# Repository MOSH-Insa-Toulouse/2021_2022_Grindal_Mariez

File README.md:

2021_2022_Grindal_Mariez_graphite_flex_sensor_project

# Objective of the project
The objective of the project is to design and build a PCB shield including a **low-tech graphite strain sensor** coupled to an analog electronic circuit that communicates data via a microcontroller to an Android application. The aim of this project is to get the resistance from a graphite sensor to measure a deformation, to analyze the results obtained and to describe the characteristics of the sensor in a datasheet.

# Main steps of the project
   [1. Graphite sensor conception](#1-graphite-sensor-conception)\
   [2. Electrical conception and simulation on *LTSpice*](#2-electronic-conception-and-test-on-ltspice)\
   [3. PCB conception and printing](#3-pcb-conception-on-kicad)\
   [4. Arduino code](#4-arduino-code)\
   [5. Application ANDROID](#5-apk-application)\
   [6. Test bed](#6-test-bed)\
   [7. Datasheet](#7-datasheet)\
   [8. Limits](#8-limits)

# 1. Graphite sensor conception
The first step is to make the graphite sensor with paper and a pencil. Pencil cores and lead mines used in mechanical pencils consist of a mixture clay and tiny scales of graphite that can slide on top of each other. The sensor outline is printed on a piece of thick printing paper, and the remaining work is simply to cut it out and fill in the dotted "U" shape with a pencil, as shown on the image below. 
<p align="center"> 

The upside is that is allows to adjust the amount of graphite by adding or erasing the pencil mark containing graphite. The downside is the difficulty of reproducing the same sensor with the same graphite layer thickness and density of graphite. An additional problem regarding graphite is presented below.

<div align="center">    

**Graphite grading scale problem**
    
<div align="left"> 
    
There exists different graphite grading scales, with the numerical scale and the HB scale the two most widely used. The HB scale goes from 9B to 9H, “H” to indicate a hard pencil and “B” to designate the blackness of the pencil’s mark, indicating a softer lead and a higher proportion of graphite.
    
The problem when trying to reproduce a sensor is the lack of a specific industry standard for the darkness of the mark to be left within the HB or any other hardness grade scale. That implies that a HB pencil from one brand will not necessarily leave the same mark as a HB pencil from another brand. Most manufacturers set their own internal standards for graphite hardness grades and some differences are regional. For example in Japan, consumers tend to prefer softer darker leads, so an HB lead produced in Japan is generally softer and darker than an HB from European producers.
    
Specifying the exact product and manufacturer in addition to the graphite grading can increase the reproductibilty of the sensor.
> This project uses graphite from BIC Criterium 550 pencils with the gradings 6B, 4B, B, H and 3H. Special STEIN HB lead mines from Pentel is also used. STEIN stands for "Strongest Technology by Enhanced SiO2 Integrated Network" and have a 10 % denser core than an average HB lead mine. This can result in a different resistance range than a normal HB pencil despite applying it the same way with the same thickness etc.

# 2. Electronic conception and test on *LTSpice*
The second step is to build the electrical circuit adapted to our case. Strain sensor is a passive sensor and needs a conditionner. The output signal od the sensor is very low and can be easily interfered by noise (from the circuit or external noise). The aim of this part is to chose the good components to have the good filters and amplifiers. We also have to take into account the chracteritic of the arduino uno card we are gonna use:
* Resolution 10 to 12 bits (1024 à 4096 points)
* Full scale (VRef) : 1.1 V to 5.0 V
* Max source impedance 1 kOhm to 10 kOhm
* Max sampling frequency 15 kHz to 2.4 MHz
 
Graphite sensor is supplied by 5 V and gives resistance values between 20 MΩ and 100 MΩ. Direct measurement of a 100 nA current does not seem feasible. We have to amplifiy the signal and to filter it.
The final electrical circuit chosen is the following:
<p align="center">

### Role of different components:
> R5 at the input protects the operational amplifier against electrostatic discharges (ESD), and together with C1 makes up a filter for voltage noises
> 
> C1 with R1 makes up a filter for the current noise
>
> R2 is replaceable, in order to allow an adaptaion of the full scale range (digital potentiometer)
>
> C4 with R3 makes up the active filter
>   
> C2 with R6 makes up the passive output filter
>   
> C3 filters out the power supply noise
>   
> The digital potentiometer MCP41050 can change the gain and adapt it to the resistance value from the graphite sensor. Resistance of the digital potentiometer can vary between 330 Ω and 50k Ω based on datasheet. 
 
### Sensor resistance calculation:
<p align="center">

### Low-pass filters
> For each electrical stage, we can simulate the cuttoff frequency by putting the capacity of each filter at zero:
> * Low-pass filter 1 (C4 = C2 = 0) : 16 kHz\
>      To select signals with frequency less than 10*1.5kHz (sample frequency of the arduino card) to respect Shannon criteria
> * Low-pass filter 2 (C1 = C2 = 0) : 2,1 kHz\
>      To filter noises from sector of the power supply at 50 Hz
> * Low-pass filter 3 (C1 = C4 = 0) : 1,6 kHz\
       To filter global external noises of voltage and current
 
### Main characteristics of the electrical circuit
> Global gain: from 3.13 to 127.9
>
> Global attenuation of a 50 Hz current noise: 100 dB or 10e5
>
> Offset of the LTC1050 is about 5 µV wich is acceptable because much lower than the voltage measured to ouputs of the resistance R1 of 10 mV (and the maximum offset voltage drift is about 0.05 μV/°C).

### Simulations on *LTSpice*
> Simulations on LT-Spice allowed us to:
> * To check the operation in nominal conditions
> * To check the operation in nominal conditions
> * To accept the impact of the LTC1050C amplifier offset
> * To accept the impact of the amplifier input current
> * To find the cuttoff frequency of each low-pass filter stage
> * To find the global attenuation of a 50 Hz current noise
> * To find the global attenuation of a current noise occurring at the aliasing limit frequency
>
> To check all these points, we did differents simulations:
> * In transient conditions, with a pulse signal from the sensor
> * In AC conditions, to see attenuation, gain and cuttoff frequencies
> * In transient conditions, with AC voltage generator to simuate 50 Hz noise.
> * In transient and AC conditions with resistance of the digital potentiometer varying from 1 kΩ to 15 kΩ (step of 1 kΩ) to see the influence of this component on ccircuit response.
<div align="center"> 

**Transient simulation with R2 varying between 1 kΩ to 15 kΩ**

   **Transient simulation with with R2 varying between 1 kΩ to 15 kΩ and noise at 50 Hz (oscillations)**
   <div align="left">   

> The digital potentiometer has a strong influence on electrical circuit. The gain is modified, but not into a linear way with potentiometer variation. The more the resistance is high, the less is the gain, and the worse is the output signal (see [Limits](#8-limits) section)

The folder 
   [Electrical simulations on LT-Spice](https://github.com/MOSH-Insa-Toulouse/2021_2022_Grindal_Mariez/tree/main/Electrical%20simulations%20on%20LT-Spice) 
   contains the LT-Spice files used into different simulations. 

# 3. PCB conception on _KiCad_
Once the electrical circuit is done, we have to make the PCB conception to get the final circuit. First, we did the schematic in *KiCad*. Then, we build the PCB plane by adding the references and dimensions of each components. The final step is to print the PCB card with different processes.
Circuit conception was made on *KiCad*. 
### Circuit schematic on *KiCad*
> The electrical circuit was made in KiCad. All pins and connections are established. For each components, we have to associate the print. For LTC1050, rotary encoder, digital potentiometer and OLED screen, we have to create our own print in our own library. The schematic is made from a model with Arduino Uno shield to have directtly the right pins and the good dimensions of the card.
>  
<p align="center">

### PCB conception on _KiCad_
> After doing the schematic, we draw the PCB with the previous dimensions :
> * Track length = 0.9 mm
> * Isolation width = 0.7 mm
> * Pad dimensions for OLED, Bluetooth module and rotary encoder = 2 mm * 2.5 mm
> * Drill size for OLED, bluetooth module, rotary encoder, AOP and digital potentiometer = 1 mm
> * Pad size for AOP and digital potentiometer = 1.8 mm * 2.5 mm
> * Drill size for resistances and capacities = 2 mm
> * Pad size for resistances and capacities = 0.8 mm
> For each component, we have to find the print associated or to make it into a new libary (for rotary encoder, OLED screen, LTC1050 and digital potentiomter). After placing the components in the optimal way, we trace the wires and make the ground plane.
> 
<p align="center">

### PCB 3D visualisation  
> 

> A 3D visualisation is possible and allowed us to well arrange components placement without spatial conflict. 

All *KiCad* files are in the folder [Projet2022_grindal_mariez_pcb](https://github.com/MOSH-Insa-Toulouse/2021_2022_Grindal_Mariez/tree/main/Projet2022_grindal_mariez_pcb)
   section.

### PCB printing processes
> Mask printed on transparent film (PCB plan from KICAD) 
>
> The mask is placed on a plate of copper convered with photo-sensitive film. The mask and the plate are insolated with UV. The black part of the mask protects the photo-sensitive resin from UV, and the clear zone of the mask reveals copper beacause photo-sensitive resin reacts with UV.
>
> PCB plate is washed with a developper solution (oxydied water) that reveals the PCB circuit
>
> PCB plate is placed in oxyde bath to remove the unwanted copper not protected by photo-sensitive zone left.
>
> PCB is washed and left to dry.

<div align="center"> 

**Final PCB circuit with all components and modules. The two wires (at right, in purple) are  \
   connected to the two pads of the graphite sensor with clamps.**
<div align="left"> 
    
# 4. Arduino code
### Improvement potential for Arduino code
> Make the code run faster and more smoothly by optimizing menu management code. This can be done by decreasing the lines of code for the OLED display and assure the switch button on the rotary encoder, which is not connected to an interrupt pin, is detected regardless of the speed of the executing loop.  The number of variables in use for the menu, submenu and blocking the rotary encoder when needed should be reduced. Suboptimal solutions to ensure the screen is refreshed correctly can be improved upon.
>
> Decrease the time interval between two measurements, currently at 700 ms, to see how fast it can measure and decrease response time.
    
### General structure of Arduino code
>The Arduino code (.ino) is written in C++ with an addition of special methods and functions.
The main text editing program used for this project is the Arduino Integrated Development Environment (IDE). It has a clean and simple interface with the option of showing a serial monitor and a serial plotter. The serial monitor is useful for checking the outcoming bytes from the board to the digital potentiometer MCP41050 and communication with the APK application via the Bluetooth module HC-05.
    
### Libraries used 
> SoftwareSerial.h for defining serial ports on specific pins, here used with the Bluetooth module and digital potentiometer.
>
> Adafruit_GFX.h and Adafruit_SSD1306.h for the I2C OLED display SBC-OLED01.
>
> Wire.h contain the definitions for I2C pins used to communicate with the OLED display.
>
> SPI.h is used to communicate with SPI devices, with Arduino as the master device. The Serial Peripheral Interface (SPI) is a synchronous serial data protocol and is used with the digital potentiometer.

### The Arduino code is divided into four parts:
>The first lines contain inclusions (#include) of libraries, definitions (#define), which is a C++ component that allows to give a name to a constant value before the program is compiled, and declarations of global variables.
>    
>The setup() function, which initializes and sets the initial values, is executed only one time after powering on the Arduino board. 
In this case, the mode of pins on the board are initialized with pinMode(), and digitalWrite() is used to turn on the pullup resistors for the rotary encoder KY-040. Data transfer through serial ports, SPI, SoftwareSerial and Serial, is enabled.
>    
>The loop() function is the main part and runs continuously after the setup until the reset button is pressed or the power supply is cut.
    It is far from optimized and contain a lot of if-statements. First it checks to detect a change in the switch button, then checks if the APK application has asked for measurement data or an updated Rcal value to update the gain. Then it does a measurement if the interval requirement is met. The last part of the loop is a mix of rotary encoder and OLED display to make the menu and submenu options work. 
>  
>The last part is constituted of definitions of the functions used in the loop function. Six functions are defined. 
>   * The first function reads the analog pin connected to the sensor called readSensor() and returns the voltage in the range 0–5 V. 
>   * Two functions manages the digital potentiometer, setPot() and potSwiper(). setPot() changes dig. pot. position and updates Rcal and gain. potSwiper() uses setPot() and takes a float as input, with the goal to land on approximately the right voltage by running through the positions to find an adequate resistance value. 
>   * The OLEDstartup() function is simply the startup screen sequence, lasting around two seconds.
>   * The last functions doEncoderA() and doEncoderB() is attached to interrupts on both pins for the rotary encoder and includes debouncing, ensuring a rapid and accurate response to manual rotation of the encoder. The variable maxRot ensures a circular list regardless of scrolling through the menu or manually adjusting the gain.

Arduino code is available in the [Arduino code](https://github.com/MOSH-Insa-Toulouse/2021_2022_Grindal_Mariez/tree/main/Arduino%20code)
   section.
  
# 5. APK application
The APK application, working on Android smartphones, is made with the free web application integrated development environment MIT App Inventor.The app communicates over Bluetooth with the HC-05 module mounted on the Arduino shield, and allows to measure and trace resistance and voltage over time.
Main features:
* Display measured voltage and resistance numerically and traced as a function of time
* Update gain if modified on the shield
* Save measured data points in a text file found in the paths "/savedRfile.txt" and "/savedVfile.txt"
    
<p align="center"> 

The application folders .apk and .api are  available in the [Application](https://github.com/MOSH-Insa-Toulouse/2021_2022_Grindal_Mariez/tree/main/Application)
   folder.
 
# 6. Test bed
The six sensors were tested under compressive and tensile deflection on cylindrical objects with a constant diameter. The test bed consisted of seven cylindral objects with each a diameter ranging from 7 cm to 1,15 cm. The contact surface was covered in paper to minimize interactions between the object and the graphite layer on the sensor under compressive deflection.

### Test procedure
> The sensor was connected to the shield with two alligator clips. Voltage measurements indicated if the start voltage was near the extreme values of the range 0-5 V, indicating signal saturation in case of very high voltage and no current flowing in case of 0 V. Saturation of the signal was handled by choosing the "set gain" option in the menu to automatically adjust the gain to start at around 1 V. No signal was fixed by applying more graphite on the dotted area of the sensor.
>
> The R0 at zero derformation was measured when the sensor was pressed flat.
>
> Each sensor was first tested under tensile deflection, that is the graphite facing away from the curvature, with the assumption that the compressive deflection is more damaging to the sensor. The tensile deflection increases the distance between the graphite layers and decreases the measured voltage. The measurements were done in the order of decreasing diameter, starting with the smallest deformation to bend the paper sensor as little as possible to avoid detoriation.
>
> Graphite was reapplied on top of the old layer and a new R0 was measured when pressed flat.
> The same procedure was repeated for the compressive deflection with the sensor laying on a flat surface graphite layer up and bent upwards around the object while pressing the object gently downwards close to the edge of the table where the alligator clips were aligned. To avoid smearing of the graphite layer, especially for the 4B and 6B pencils, minimal friction was ensured between the sensor and the paper covered object. It is possible that smearing would have a minimal impact because the layer applied was thick. The measurements were done in the order of decreasing diameter, starting with the smallest deformation. 
>
> For compressive deflection, sudden drops in voltages occured for some of the sensors when repedately bending around the smallest objects and inducing large deformations. In those cases, graphite was reapplied on top of the old layer, a new R0 was measured when pressed flat and a new measurement series was conducted starting with the largest object.
    
# 7. Datasheet
Datesheet is providing the main characteristics and technical specifications of the strain sensor. It is in the folder [Datasheet](https://github.com/MOSH-Insa-Toulouse/2021_2022_Grindal_Mariez/tree/main/Datasheet)
   of the repository. 

# 8. Limits
   Is important to notice the limits of the sensor and the innacuracy of the test measures. Here are main points to be studied or solved:
   * The digital potentiometer MCP41050 is perfectly adapted to the graphite sensor. It would be better to have a sensor with a resistance variation between 10 Ω to 15 Ω, as the MCP41010 from *Microchip* for example.
   * The mapping from 8 bits to 10 bits in arduino code may lead to a resolution loss, so we lose in quality for the signal. 
   * We need a switch button to interrupt in case of problems
   * Regarding test bed, we are never sure of the amount of deposited graphite and it is not uniform. Also, the graphite quantity variation is not linear with pencils changing. Finally, paper is damaged after several compression/tension, so the measures are never similar

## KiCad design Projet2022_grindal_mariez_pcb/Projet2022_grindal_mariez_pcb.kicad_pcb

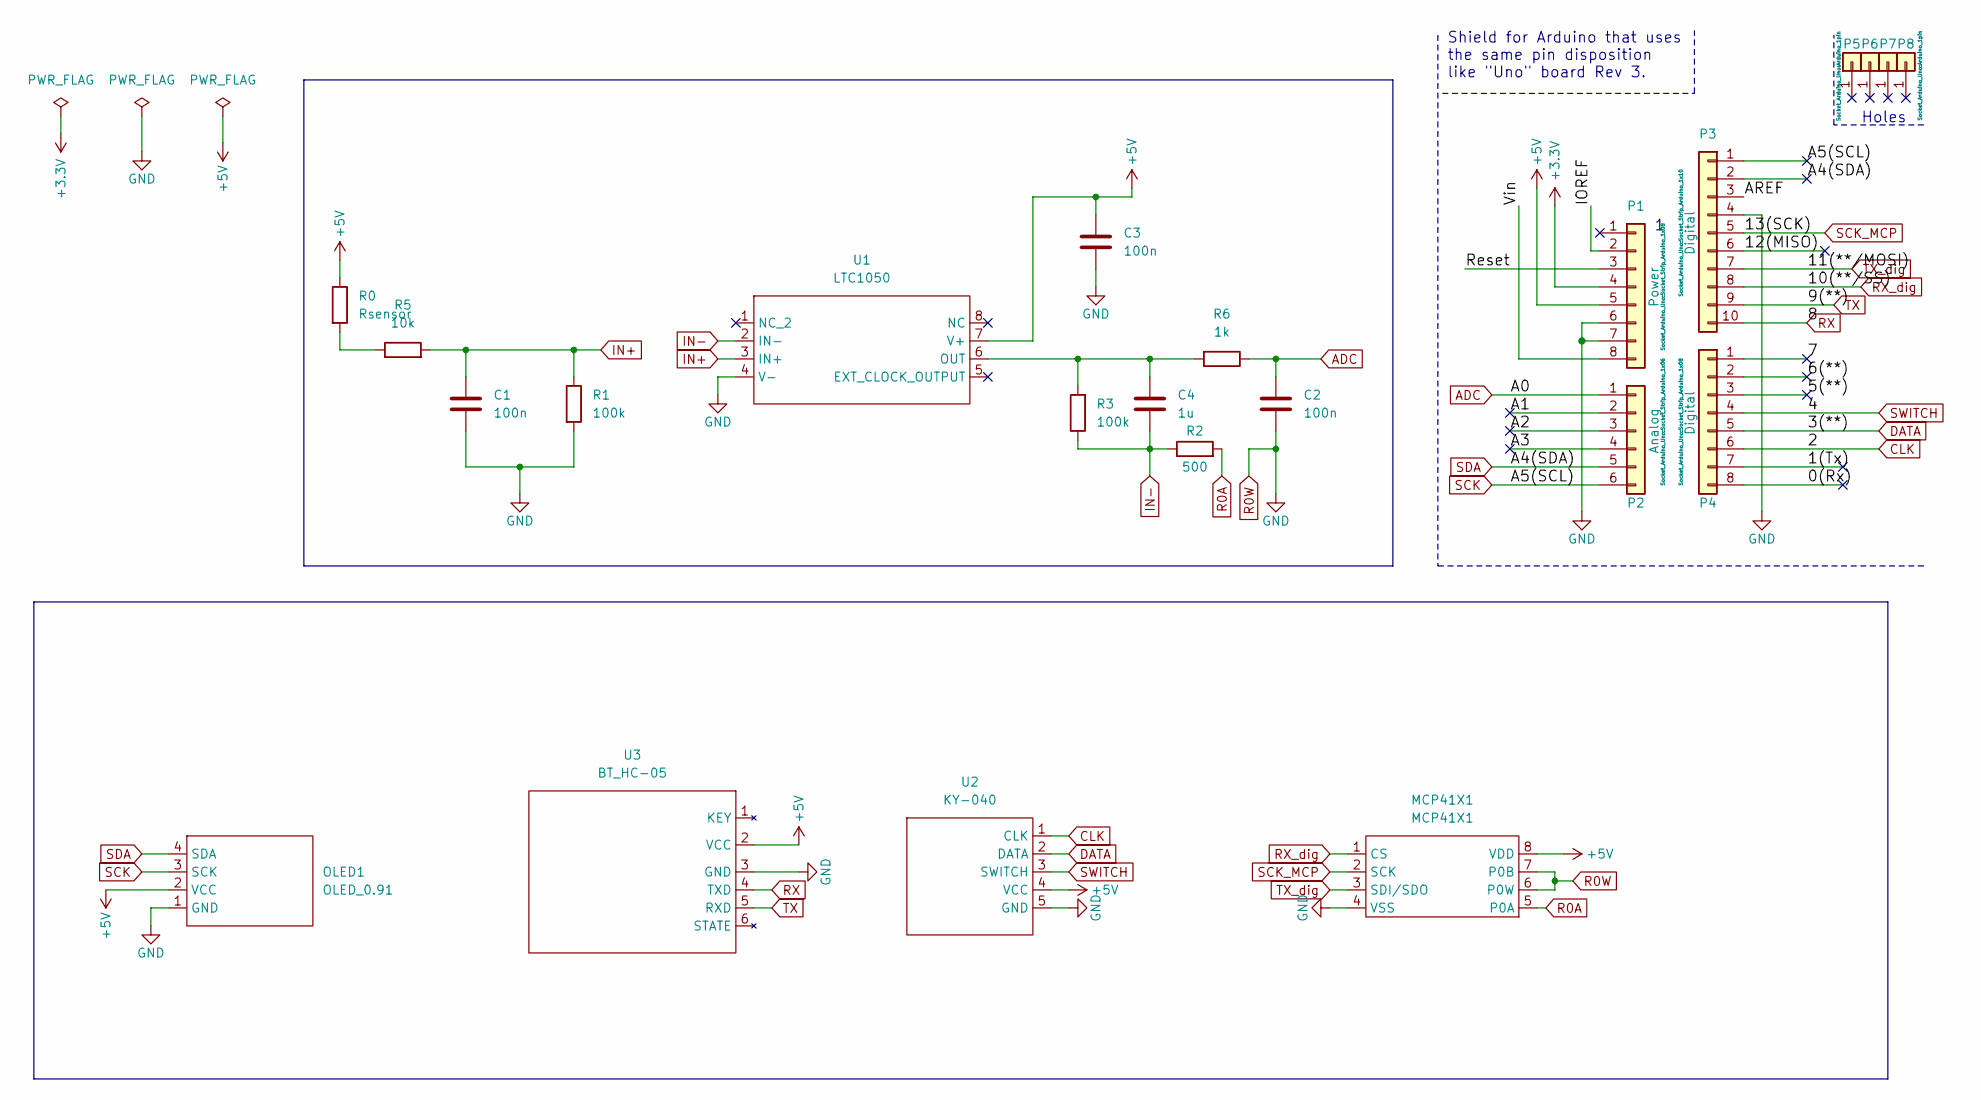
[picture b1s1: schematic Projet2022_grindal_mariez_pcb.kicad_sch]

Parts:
C1, C2, C3: 100n; C_Disc_D7.0mm_W2.5mm_P5.00mm
C4: 1u; C_Rect_L7.0mm_W2.0mm_P5.00mm
MCP41X1: MCP41X1; MCP41050
OLED1: OLED_0.91
P1: Power; Socket_Strip_Arduino_1x08
P2: Analog; Socket_Strip_Arduino_1x06
P3: Digital; Socket_Strip_Arduino_1x10
P4: Digital; Socket_Strip_Arduino_1x08
P5, P6, P7, P8: CONN_01X01; Arduino_1pin
R0: Rsensor; R_Axial_DIN0207_L6.3mm_D2.5mm_P10.16mm_Horizontal
R1, R3: 100k; R_Axial_DIN0207_L6.3mm_D2.5mm_P10.16mm_Horizontal
R2: 500; R_Axial_DIN0207_L6.3mm_D2.5mm_P10.16mm_Horizontal
R5: 10k; R_Axial_DIN0207_L6.3mm_D2.5mm_P10.16mm_Horizontal
R6: 1k; R_Axial_DIN0207_L6.3mm_D2.5mm_P7.62mm_Horizontal
U1: LTC1050; LTC1050C
U2: KY-040; KY_040
U3: BT_HC-05; BT_HC05

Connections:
+3V3: P1.4
+5V: C3.2, MCP41X1.8 (VDD), OLED1.2 (VCC), P1.5, R0.1, U1.7 (V+), U2.4 (VCC), U3.2 (VCC)
/0(Rx): P4.8
/1(Tx): P4.7
/5(**): P4.3
/6(**): P4.2
/7: P4.1
/12(MISO): P3.6
/A1: P2.2
/A2: P2.3
/A3: P2.4
/AREF: P3.3
/IOREF: P1.2
/Reset: P1.3
/Vin: P1.8
ADC: C2.1, P2.1, R6.1
CLK: P4.6, U2.1 (CLK)
DATA: P4.5, U2.2 (DATA)
IN+: C1.1, R1.1, R5.2, U1.3 (IN+)
IN-: C4.2, R2.1, R3.1, U1.2 (IN-)
unnamed: C4.1, R3.2, R6.2, U1.6 (OUT)
unnamed: R0.2, R5.1
R0A: MCP41X1.5 (P0A), R2.2
R0W: C1.2, C2.2, C3.1, MCP41X1.4 (VSS), MCP41X1.6 (P0W), MCP41X1.7 (P0B), OLED1.1 (GND), P1.6, P1.7, P3.4, R1.2, U1.4 (V-), U2.5 (GND), U3.3 (GND)
RX: P3.10, U3.4 (TXD)
RX_dig: MCP41X1.1 (CS), P3.8
SCK: OLED1.3 (SCK), P2.6, P3.1
SCK_MCP: MCP41X1.2 (SCK), P3.5
SDA: OLED1.4 (SDA), P2.5, P3.2
SWITCH: P4.4, U2.3 (SWITCH)
TX: P3.9, U3.5 (RXD)
TX_dig: MCP41X1.3 (SDI/SDO), P3.7

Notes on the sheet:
Holes
Shield for Arduino that uses the same pin disposition like "Uno" board Rev 3.

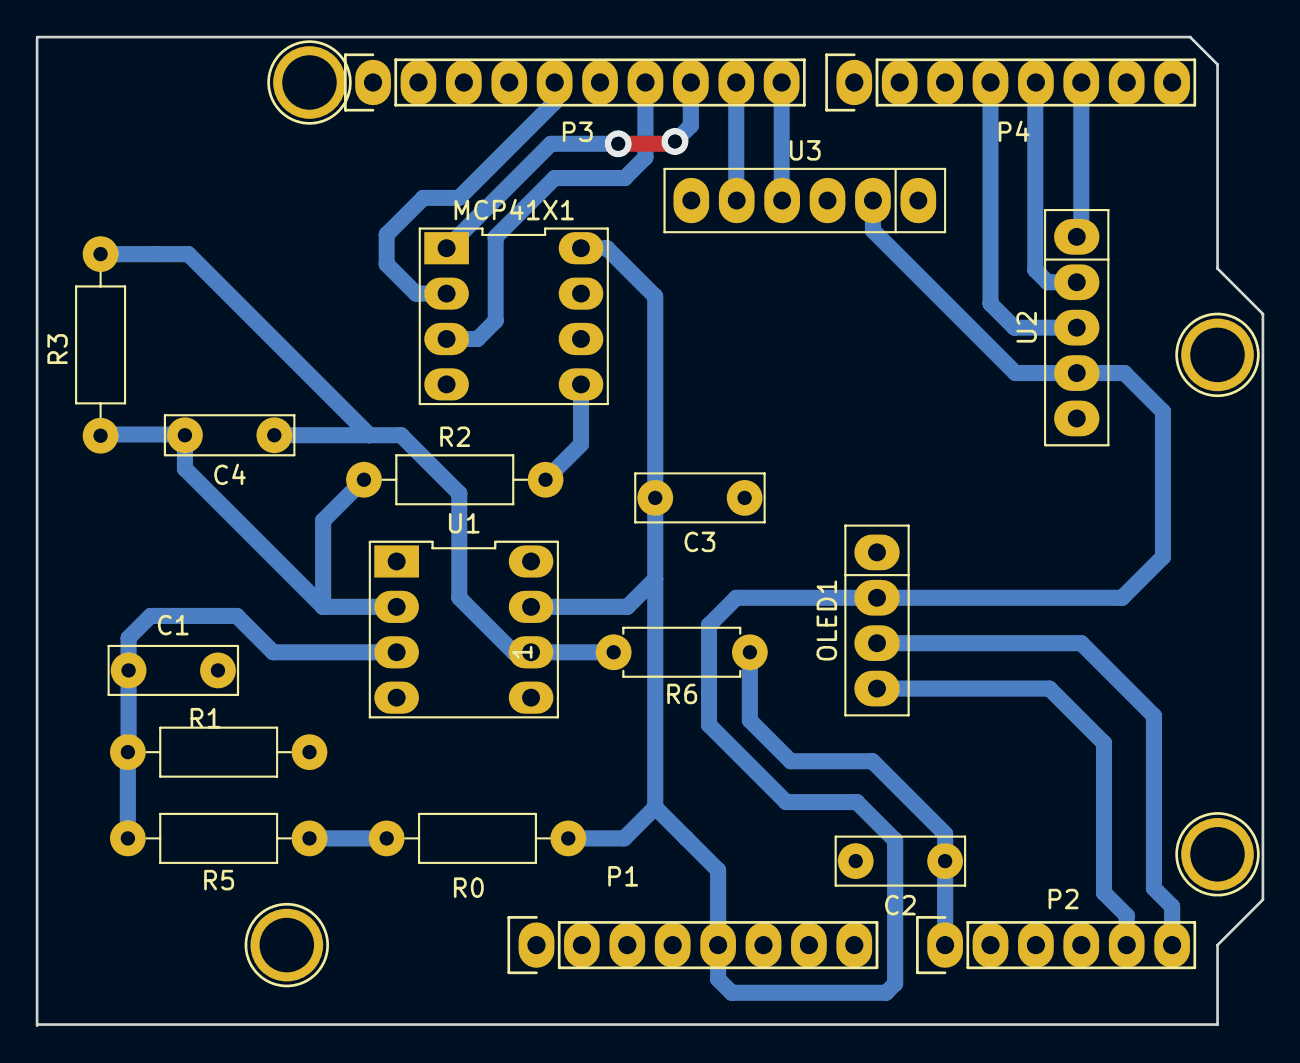
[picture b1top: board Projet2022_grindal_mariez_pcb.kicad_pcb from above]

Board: 2 copper layers, 68.6 x 55.3 mm, 23 parts (0 on the bottom side), 18 nets.

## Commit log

2022-04-14 Create Illustrations
2022-04-14 Update Illustrations
2022-04-14 Create picture1
2022-04-15 Create brouillon
2022-04-15 Create testtes
2022-04-15 Create doc
2022-04-18 Update README.md
    Description of Arduino code
2022-04-19 Add files via upload
    fix update gain in apk app
2022-04-21 Create adc
2022-04-26 Create gafd
2022-05-13 Create uiyacd
